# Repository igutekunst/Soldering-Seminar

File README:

Soldering Projects and code to teach new people about Electronics.

Directory structure is as follows:

Projects:
	Contains each individual project

projects/projectName      : Projects are all submodules to make things simpler 
	/eagle		: pcb files
	/firmware	: all code necessary to run hardware (excludes computer side code)
	/eagleUp	: files necessary to make a 3D model of the board
	/gerbers	: output RS-274X files to send to the manufacturer
	/datasheets	: data sheets specific to project

eagle-config:
	Special eagle files, such as a custom library, and some design rules

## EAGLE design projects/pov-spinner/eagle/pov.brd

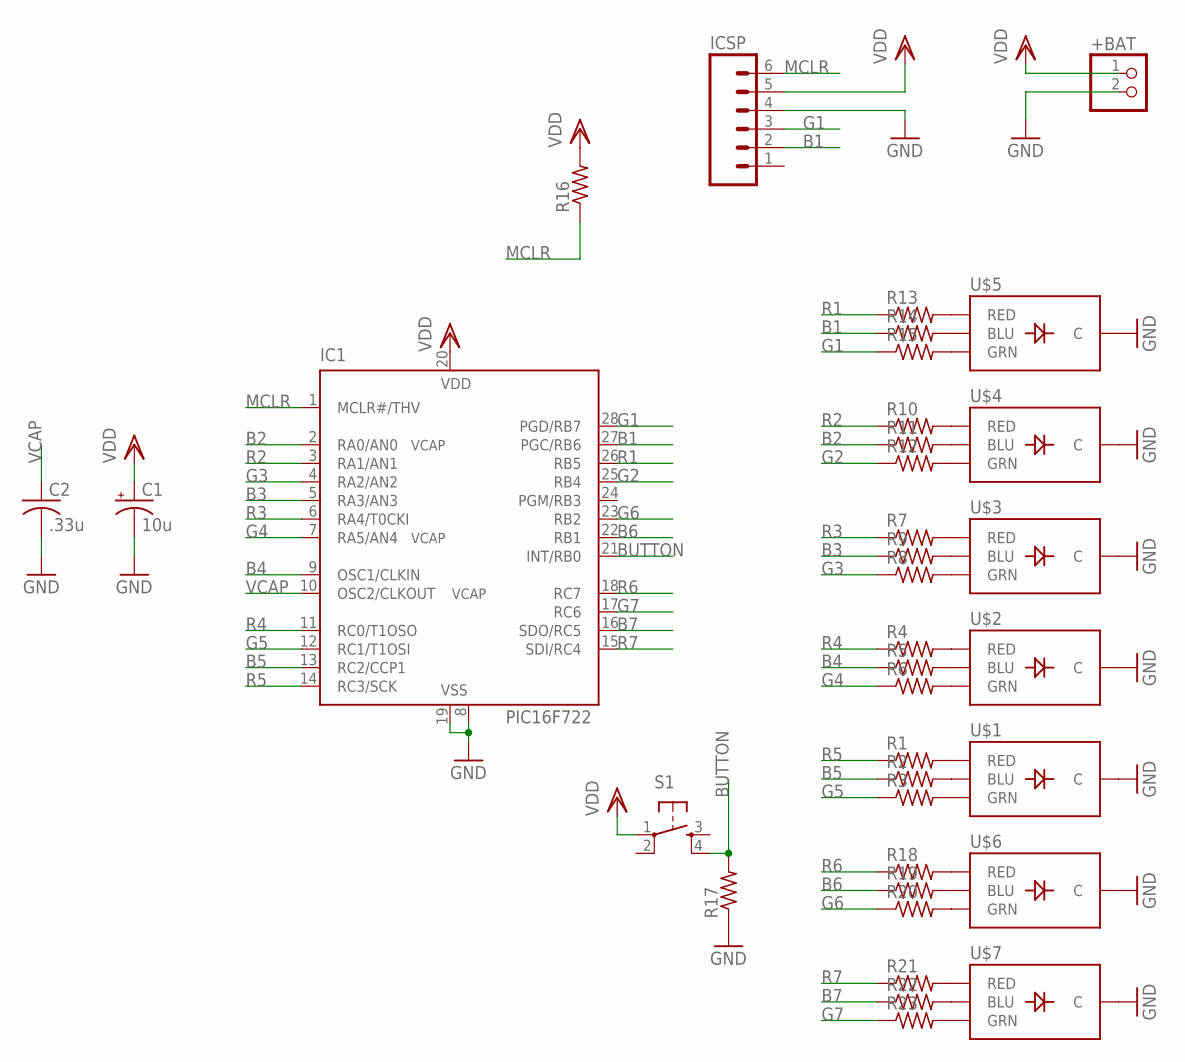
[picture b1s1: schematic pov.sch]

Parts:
+BAT: PINHD-1X2; 1X02
C1: 10u; CPOL-RADIAL-10UF-25V
C2: .33u; C050-024X044
IC1: PIC16F722; DIL28-3
ICSP: M06LOCK; 1X06_LOCK
R1, R2, R3, R4, R5, R6, R7, R8, R9, R10, R11, R12, R13, R14, R15, R16, R17, R18, R19, R20, R21, R22, R23: R-US_0207/10; 0207/10
S1: TAC_SWITCHPTH; TACTILE-PTH
U$1, U$2, U$3, U$4, U$5, U$6, U$7: LED-TRICOLOR-THROUGHHOLE

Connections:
B1: IC1.27 (PGC/RB6), ICSP.2, R14.1
B2: IC1.2 (RA0/AN0), R11.1
B3: IC1.5 (RA3/AN3), R9.1
B4: IC1.9 (OSC1/CLKIN), R5.1
B5: IC1.13 (RC2/CCP1), R2.1
B6: IC1.22 (RB1), R19.1
B7: IC1.16 (SDO/RC5), R22.1
BUTTON: IC1.21 (INT/RB0), R17.2, S1.4
G1: IC1.28 (PGD/RB7), ICSP.3, R15.1
G2: IC1.25 (RB4), R12.1
G3: IC1.4 (RA2/AN2), R8.1
G4: IC1.7 (RA5/AN4), R6.1
G5: IC1.12 (RC1/T1OSI), R3.1
G6: IC1.23 (RB2), R20.1
G7: IC1.17 (RC6), R23.1
GND: +BAT.2, C1.2 (-), C2.2, IC1.8 (VSS), IC1.19 (VSS), ICSP.4, R17.1, U$1.GND (C), U$2.GND (C), U$3.GND (C), U$4.GND (C), U$5.GND (C), U$6.GND (C), U$7.GND (C)
MCLR: IC1.1 (MCLR#/THV), ICSP.6, R16.1
unnamed: R1.2, U$1.RED
unnamed: R2.2, U$1.BLU
unnamed: R3.2, U$1.GRN
unnamed: R4.2, U$2.RED
unnamed: R5.2, U$2.BLU
unnamed: R6.2, U$2.GRN
unnamed: R7.2, U$3.RED
unnamed: R9.2, U$3.BLU
unnamed: R10.2, U$4.RED
unnamed: R11.2, U$4.BLU
unnamed: R12.2, U$4.GRN
unnamed: R13.2, U$5.RED
unnamed: R14.2, U$5.BLU
unnamed: R15.2, U$5.GRN
unnamed: R8.2, U$3.GRN
unnamed: R18.2, U$6.RED
unnamed: R19.2, U$6.BLU
unnamed: R20.2, U$6.GRN
unnamed: R21.2, U$7.RED
unnamed: R22.2, U$7.BLU
unnamed: R23.2, U$7.GRN
R1: IC1.26 (RB5), R13.1
R2: IC1.3 (RA1/AN1), R10.1
R3: IC1.6 (RA4/T0CKI), R7.1
R4: IC1.11 (RC0/T1OSO), R4.1
R5: IC1.14 (RC3/SCK), R1.1
R6: IC1.18 (RC7), R18.1
R7: IC1.15 (SDI/RC4), R21.1
VCAP: C2.1, IC1.10 (OSC2/CLKOUT)
VDD: +BAT.1, C1.1 (+), IC1.20 (VDD), ICSP.5, R16.2, S1.1

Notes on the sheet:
VCAP

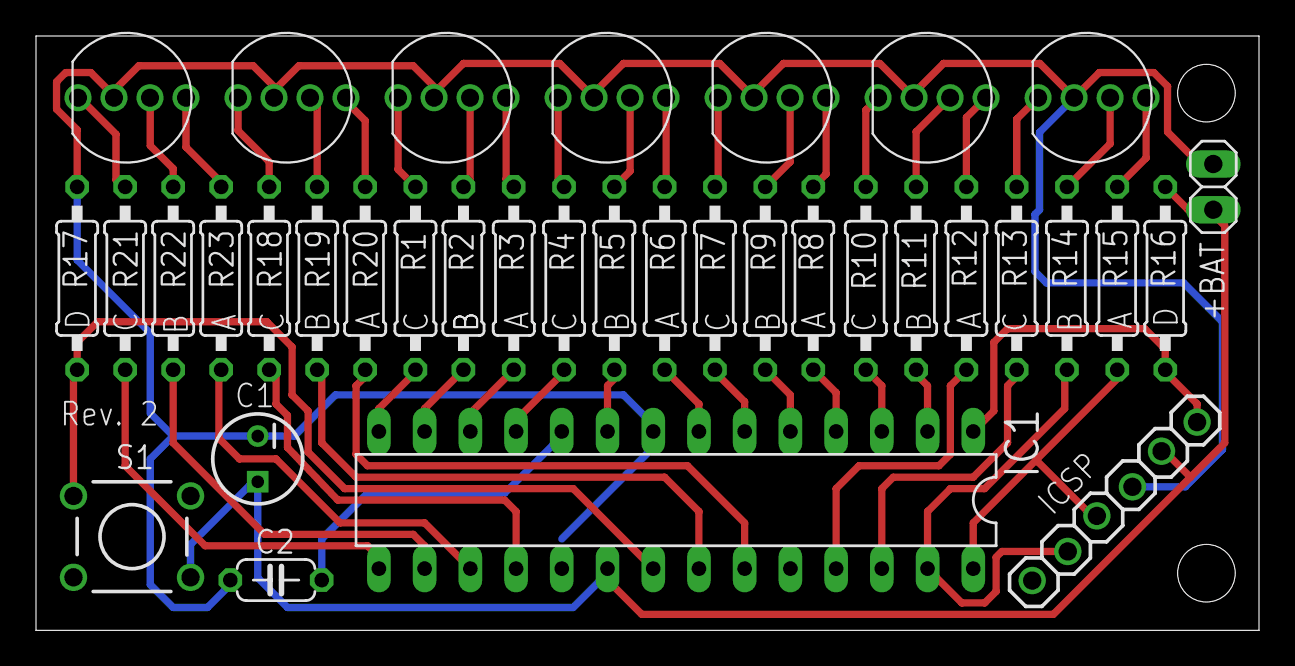
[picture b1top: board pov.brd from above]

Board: 2 copper layers, 67.9 x 33.0 mm, 37 parts (1 on the bottom side), 47 nets.

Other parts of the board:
U$8: DONLAN_2

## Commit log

2012-02-25 Added three projects, and setup basic directory structure
2012-02-25 added a .gitignore file so we don't have to deal with annoying files
2012-02-25 fixed .gitignore a bit
2012-02-25 hopefully fixed the submodule problem
2012-02-25 stopeed tracking dumb build files
2012-02-25 removed terrible firmware
2012-02-25 added the laser tag firmware correctly
2012-02-25 got rid of laser tag to try out submodules
2012-02-25 Added Laser-Tag submodule
2012-02-25 removed ac dimmer in preperation for a submodule
2012-02-25 added ac-dmx-dimmer submodule
2012-02-25 Updated readme to relfect submodule structure
2012-02-25 Updated the DMX submodule
2012-02-25 added sparkfun and custom library
2012-02-25 Moved the eagle data into a submodule
2012-02-25 Maybe submodules are too confusing
2012-02-25 hopefully fixed some problems with mplabx projects
2012-02-25 Git submodules are annoying when they suddenly show up
2012-02-27 Cleaning up
2012-07-24 added pov spinner code. Will remove binary stuff when I know what's going on
